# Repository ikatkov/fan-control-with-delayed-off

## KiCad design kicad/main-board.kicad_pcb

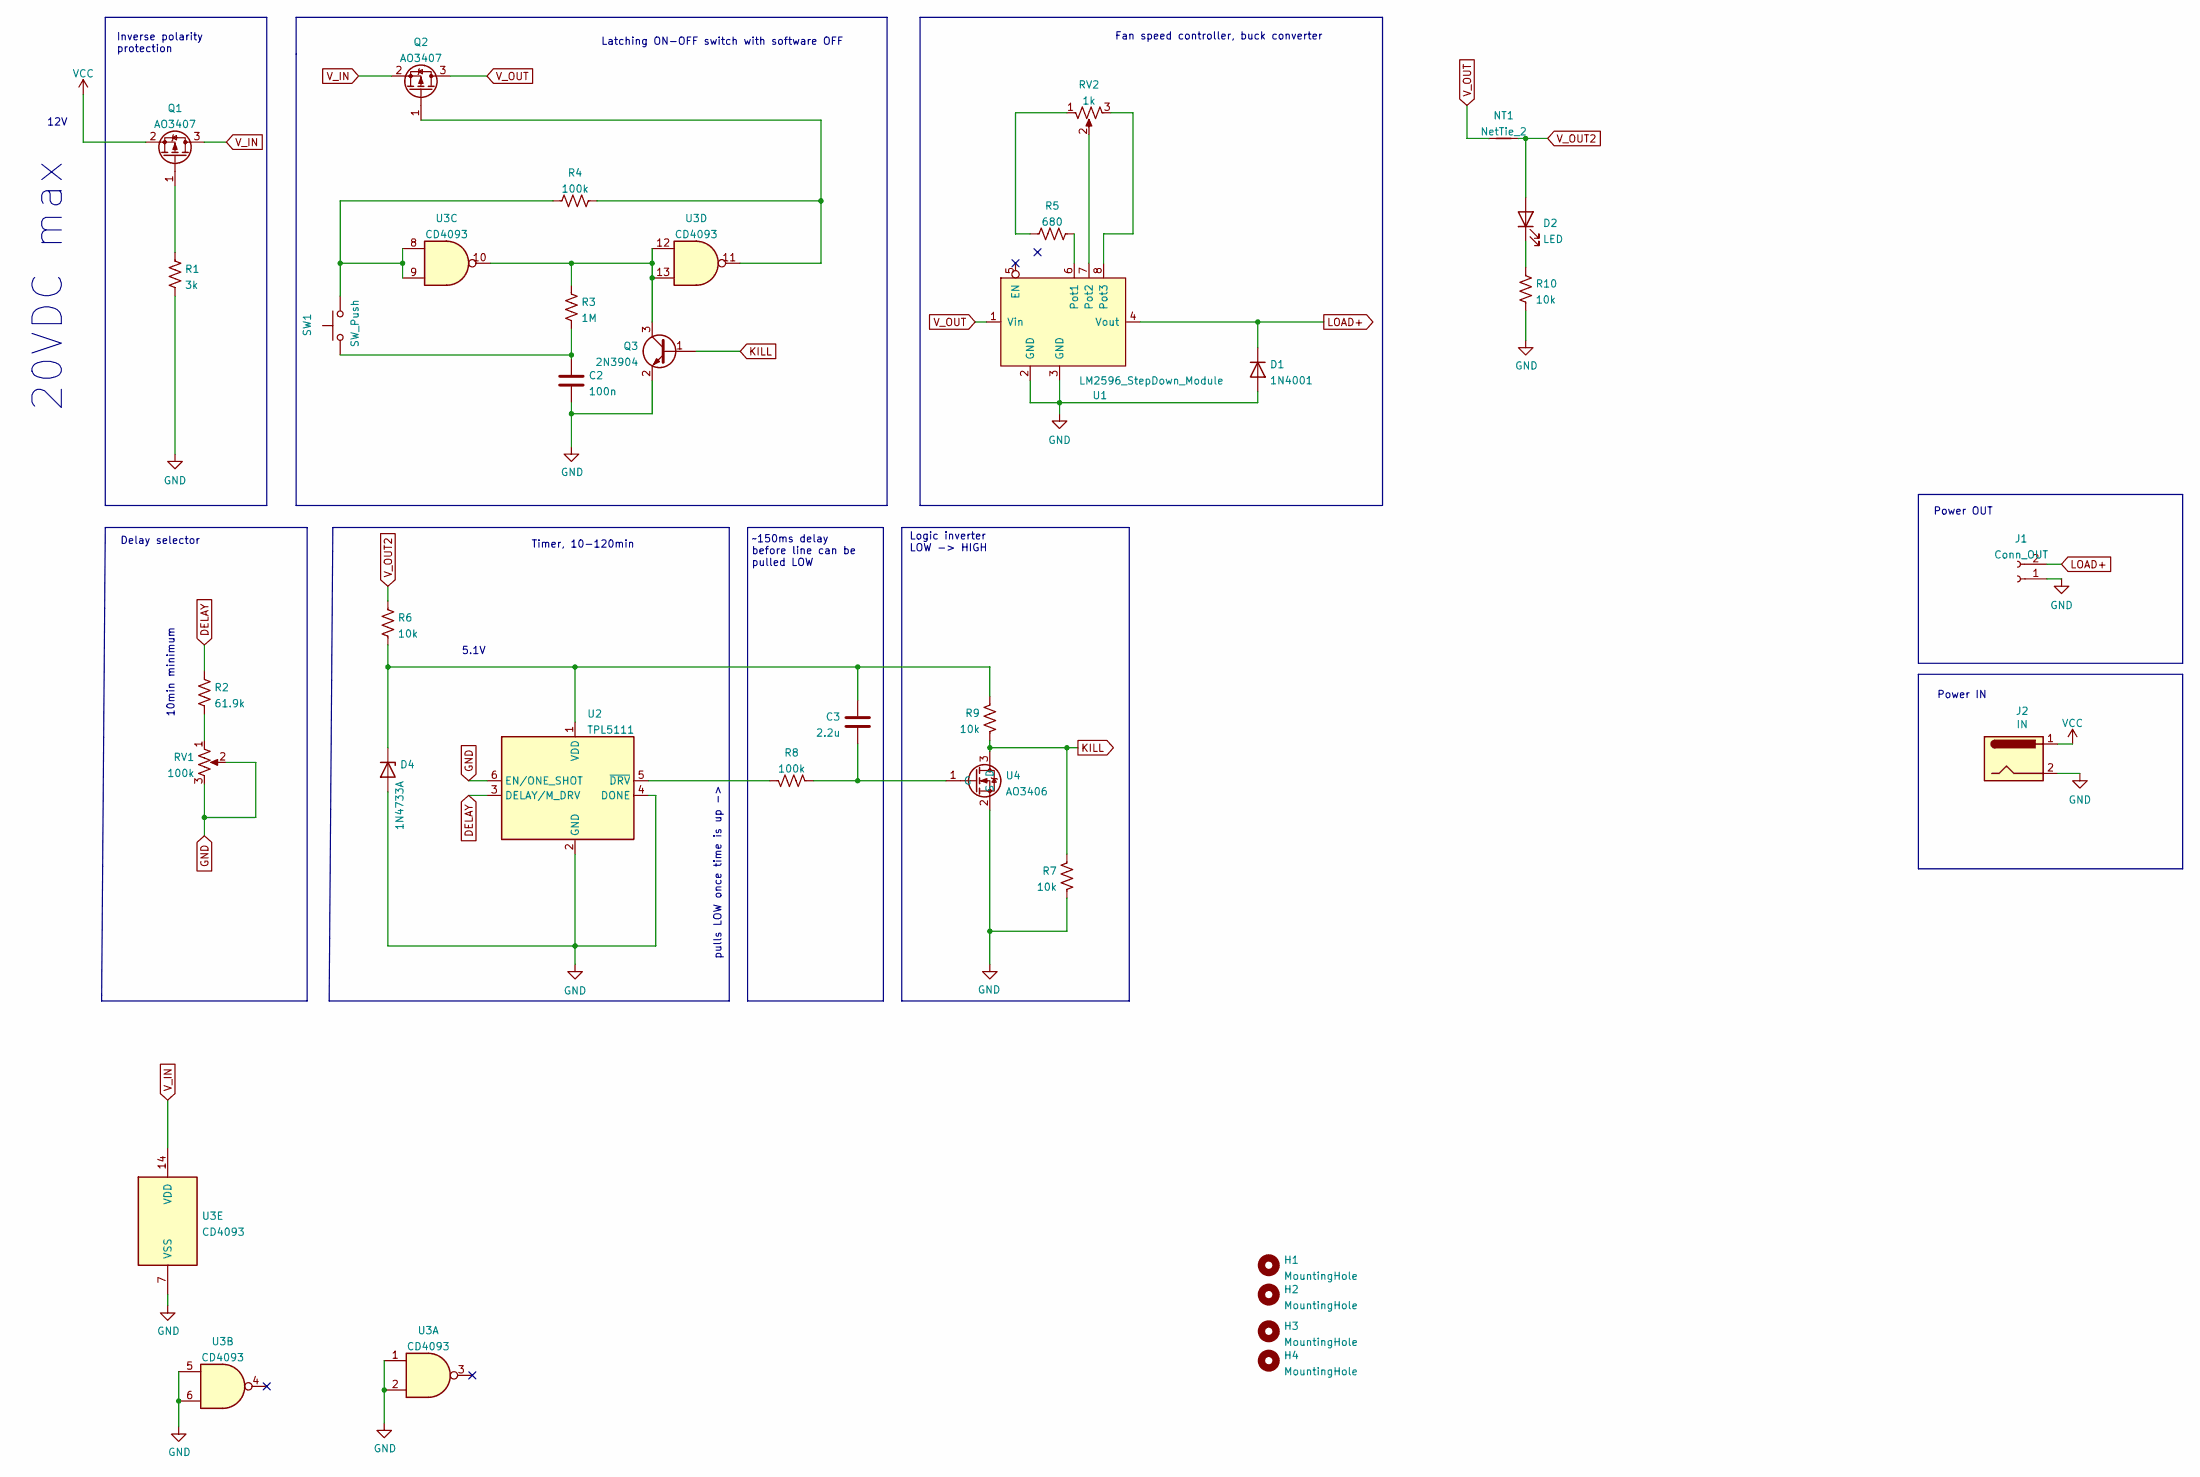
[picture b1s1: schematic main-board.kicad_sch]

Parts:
C2: 100n; C_1206_3216Metric
C3: 2.2u; C_1206_3216Metric
D1: 1N4001; D_SMB_Handsoldering
D2: LED; LED_D5.0mm
D4: 1N4733A; D_SMA_Handsoldering
H1, H2, H3, H4: MountingHole; MountingHole_3.2mm_M3
J1: Conn_OUT; TerminalBlock_bornier-2_P5.08mm
J2: IN; BarrelJack_Horizontal
NT1: NetTie_2; R_1206_3216Metric_Pad1.30x1.75mm_HandSolder
Q1, Q2: AO3407; SOT-23_Handsoldering
Q3: 2N3904; SOT-23
R1: 3k; R_0805_2012Metric_Pad1.20x1.40mm_HandSolder
R2: 61.9k; R_0805_2012Metric_Pad1.20x1.40mm_HandSolder
R3: 1M; R_0805_2012Metric_Pad1.20x1.40mm_HandSolder
R4, R8: 100k; R_0805_2012Metric_Pad1.20x1.40mm_HandSolder
R5: 680; R_0805_2012Metric_Pad1.20x1.40mm_HandSolder
R6, R7, R9, R10: 10k; R_0805_2012Metric_Pad1.20x1.40mm_HandSolder
RV1: 100k; Potentiometer_RV09_Single_Vertical
RV2: 1k; Potentiometer_RV09_Single_Vertical
SW1: SW_Push; SW_PUSH_6mm
U1: LM2596_StepDown_Module; LM2596_StepDown_pot
U2: TPL5111; SOT-23-6
U3: CD4093; SOIC-14_3.9x8.7mm_P1.27mm
U4: AO3406; SOT-23_Handsoldering

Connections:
DELAY: R2.1, U2.3 (DELAY/M_DRV)
GND: C2.2, D1.2 (A), D4.2 (A), J1.1, J2.2, Q3.2 (E), R1.1, R7.2, R10.2, RV1.2, RV1.3, U1.2 (GND), U1.3 (GND), U2.2 (GND), U2.4 (DONE), U2.6 (EN/ONE_SHOT), U3.1, U3.2, U3.5, U3.6, U3.7 (VSS), U4.2 (S)
KILL: Q3.1 (B), R7.1, R9.2, U4.3 (D)
LOAD+: D1.1 (K), J1.2, U1.4 (Vout)
unnamed: C2.1, R3.1, SW1.1
unnamed: C3.1, D4.1 (K), R6.2, R9.1, U2.1 (VDD)
unnamed: C3.2, R8.2, U4.1 (G)
unnamed: D2.1 (K), R10.1
unnamed: Q1.1 (G), R1.2
unnamed: Q2.1 (G), R4.2, U3.11
unnamed: Q3.3 (C), R3.2, U3.10, U3.12, U3.13
unnamed: R2.2, RV1.1
unnamed: R4.1, SW1.2, U3.8, U3.9
unnamed: R5.1, U1.6 (Pot1)
unnamed: R5.2, RV2.1
unnamed: R8.1, U2.5 (~DRV)
unnamed: RV2.2, U1.7 (Pot2)
unnamed: RV2.3, U1.8 (Pot3)
VCC: J2.1, Q1.2 (S)
V_IN: Q1.3 (D), Q2.2 (S), U3.14 (VDD)
V_OUT: NT1.1, Q2.3 (D), U1.1 (Vin)
V_OUT2: D2.2 (A), NT1.2, R6.1

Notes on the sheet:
Timer, 10-120min
5.1V
Delay selector
Power IN
Fan speed controller, buck converter
Inverse polarity protection
12V
10min minimum
Latching ON-OFF switch with software OFF
20VDC max
Power OUT
~150ms delay before line can be pulled LOW
pulls LOW once time is up ->
Logic inverter LOW -> HIGH

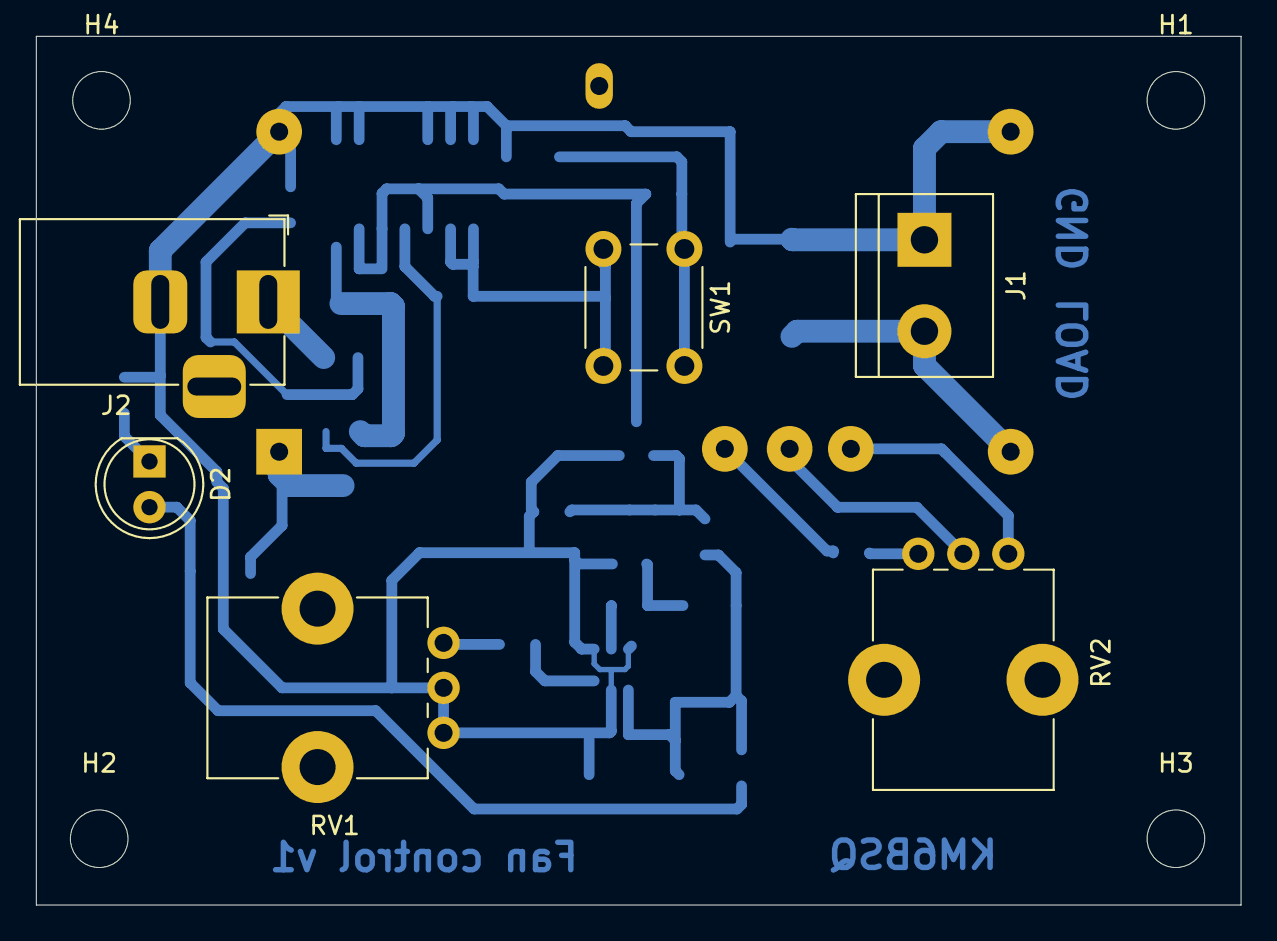
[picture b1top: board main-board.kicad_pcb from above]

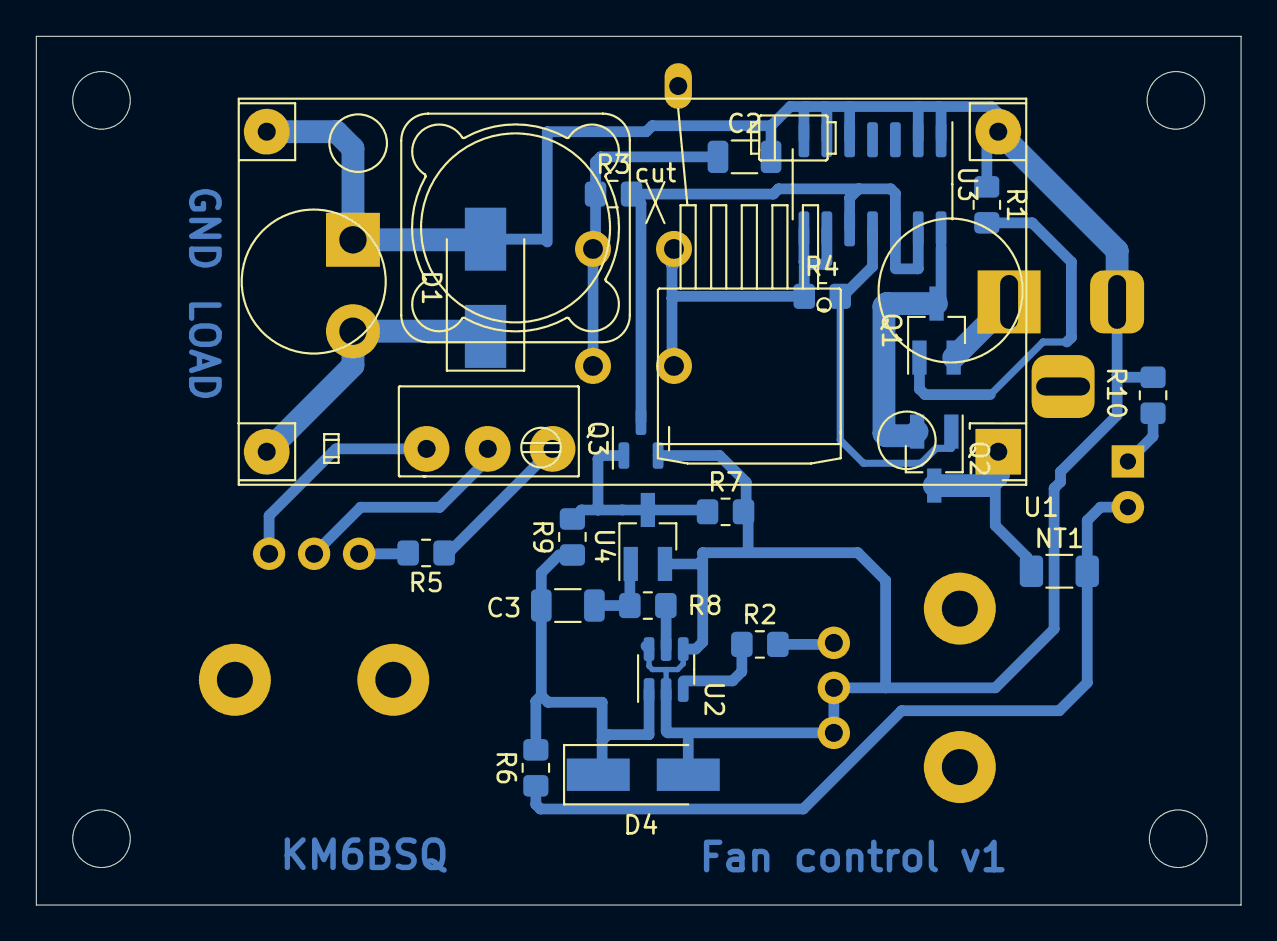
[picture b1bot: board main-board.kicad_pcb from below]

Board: 4 copper layers, 66.9 x 48.3 mm, 32 parts (22 on the bottom side), 22 nets.

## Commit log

2022-08-01 Initial
